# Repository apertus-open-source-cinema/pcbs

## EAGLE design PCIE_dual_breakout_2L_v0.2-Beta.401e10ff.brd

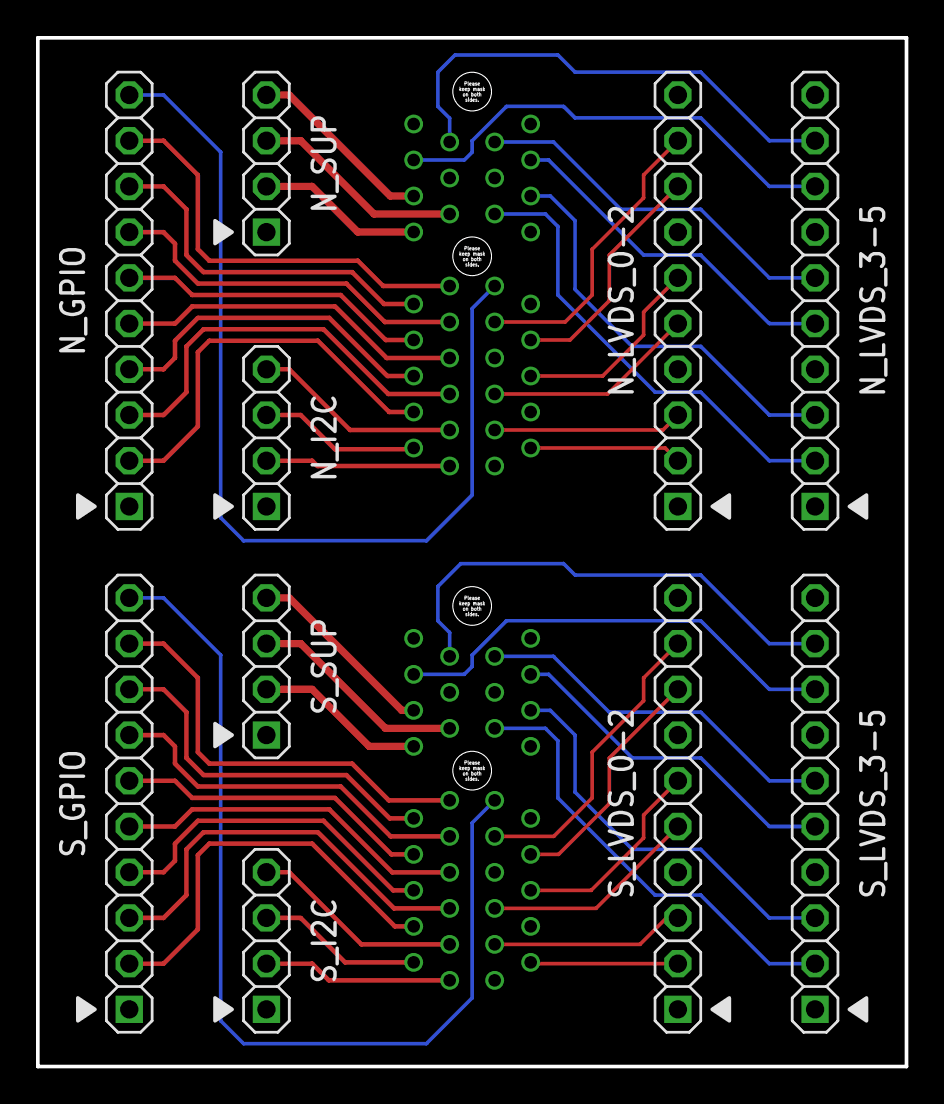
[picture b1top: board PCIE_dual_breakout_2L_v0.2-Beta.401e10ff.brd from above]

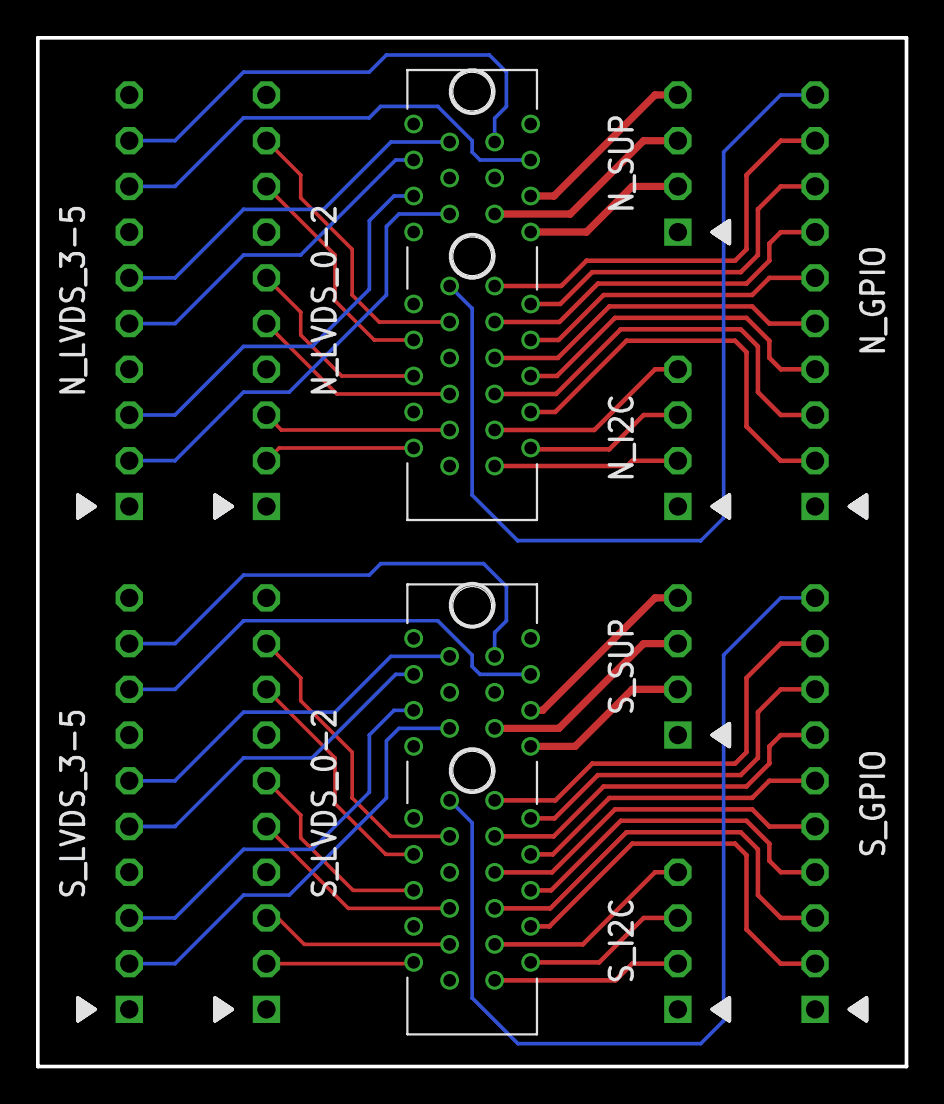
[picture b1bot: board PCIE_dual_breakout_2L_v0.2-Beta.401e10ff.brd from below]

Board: 2 copper layers, 48.3 x 57.1 mm, 12 parts (2 on the bottom side), 54 nets.

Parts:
N_GPIO: 1X10-S
N_I2C: 1X04-S
N_LVDS_0-2, N_LVDS_3-5: 1X10-S
N_SUP: 1X04-S
PCIE-NORTH: PCIE-36-AXIOM-SOCKET; PCIE-36
PCIE-SOUTH: PCIE-36-AXIOM-SOCKET; PCIE-36
S_GPIO: 1X10-S
S_I2C: 1X04-S
S_LVDS_0-2, S_LVDS_3-5: 1X10-S
S_SUP: 1X04-S

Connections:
GND: N_GPIO.1, N_I2C.1, N_LVDS_0-2.1, N_LVDS_0-2.4, N_LVDS_0-2.7, N_LVDS_0-2.10, N_LVDS_3-5.1, N_LVDS_3-5.4, N_LVDS_3-5.7, N_LVDS_3-5.10, N_SUP.1, PCIE-NORTH.A1, PCIE-NORTH.A4, PCIE-NORTH.A7, PCIE-NORTH.A10, PCIE-NORTH.A12, PCIE-NORTH.A15, PCIE-NORTH.A18, PCIE-NORTH.B15, PCIE-NORTH.B18, PCIE-SOUTH.A1, PCIE-SOUTH.A4, PCIE-SOUTH.A7, PCIE-SOUTH.A10, PCIE-SOUTH.A12, PCIE-SOUTH.A15, PCIE-SOUTH.A18, PCIE-SOUTH.B15, PCIE-SOUTH.B18, S_GPIO.1, S_I2C.1, S_LVDS_0-2.1, S_LVDS_0-2.4, S_LVDS_0-2.7, S_LVDS_0-2.10, S_LVDS_3-5.1, S_LVDS_3-5.4, S_LVDS_3-5.7, S_LVDS_3-5.10, S_SUP.1
N_LVDS_0A: N_LVDS_0-2.2, PCIE-NORTH.A2
N_LVDS_0B: N_LVDS_0-2.3, PCIE-NORTH.A3
N_LVDS_1A: N_LVDS_0-2.5, PCIE-NORTH.A5
N_LVDS_1B: N_LVDS_0-2.6, PCIE-NORTH.A6
N_LVDS_2A: N_LVDS_0-2.8, PCIE-NORTH.A8
N_LVDS_2B: N_LVDS_0-2.9, PCIE-NORTH.A9
N_LVDS_3A: N_LVDS_3-5.2, PCIE-NORTH.A13
N_LVDS_3B: N_LVDS_3-5.3, PCIE-NORTH.A14
N_LVDS_4A: N_LVDS_3-5.5, PCIE-NORTH.A16
N_LVDS_4B: N_LVDS_3-5.6, PCIE-NORTH.A17
N_LVDS_5A: N_LVDS_3-5.8, PCIE-NORTH.B16
N_LVDS_5B: N_LVDS_3-5.9, PCIE-NORTH.B17
N_PWRGD: N_GPIO.10, PCIE-NORTH.A11
PCIE_I2C_V: N_I2C.4, PCIE-NORTH.B3, PCIE-SOUTH.B3, S_I2C.4
PCIE_N_5V: N_SUP.2, PCIE-NORTH.B12
PCIE_N_IO0: N_GPIO.2, PCIE-NORTH.B4
PCIE_N_IO1: N_GPIO.3, PCIE-NORTH.B5
PCIE_N_IO2: N_GPIO.4, PCIE-NORTH.B6
PCIE_N_IO3: N_GPIO.5, PCIE-NORTH.B7
PCIE_N_IO4: N_GPIO.6, PCIE-NORTH.B8
PCIE_N_IO5: N_GPIO.7, PCIE-NORTH.B9
PCIE_N_IO6: N_GPIO.8, PCIE-NORTH.B10
PCIE_N_IO7: N_GPIO.9, PCIE-NORTH.B11
PCIE_N_SCL: N_I2C.3, PCIE-NORTH.B2
PCIE_N_SDA: N_I2C.2, PCIE-NORTH.B1
PCIE_N_V: N_SUP.3, PCIE-NORTH.B13
PCIE_N_VCCIO: N_SUP.4, PCIE-NORTH.B14
PCIE_S_5V: PCIE-SOUTH.B12, S_SUP.2
PCIE_S_IO0: PCIE-SOUTH.B4, S_GPIO.2
PCIE_S_IO1: PCIE-SOUTH.B5, S_GPIO.3
PCIE_S_IO2: PCIE-SOUTH.B6, S_GPIO.4
PCIE_S_IO3: PCIE-SOUTH.B7, S_GPIO.5
PCIE_S_IO4: PCIE-SOUTH.B8, S_GPIO.6
PCIE_S_IO5: PCIE-SOUTH.B9, S_GPIO.7
PCIE_S_IO6: PCIE-SOUTH.B10, S_GPIO.8
PCIE_S_IO7: PCIE-SOUTH.B11, S_GPIO.9
PCIE_S_SCL: PCIE-SOUTH.B2, S_I2C.3
PCIE_S_SDA: PCIE-SOUTH.B1, S_I2C.2
PCIE_S_V: PCIE-SOUTH.B13, S_SUP.3
PCIE_S_VCCIO: PCIE-SOUTH.B14, S_SUP.4
S_LVDS_0A: PCIE-SOUTH.A2, S_LVDS_0-2.2
S_LVDS_0B: PCIE-SOUTH.A3, S_LVDS_0-2.3
S_LVDS_1A: PCIE-SOUTH.A5, S_LVDS_0-2.5
S_LVDS_1B: PCIE-SOUTH.A6, S_LVDS_0-2.6
S_LVDS_2A: PCIE-SOUTH.A8, S_LVDS_0-2.8
S_LVDS_2B: PCIE-SOUTH.A9, S_LVDS_0-2.9
S_LVDS_3A: PCIE-SOUTH.A13, S_LVDS_3-5.2
S_LVDS_3B: PCIE-SOUTH.A14, S_LVDS_3-5.3
S_LVDS_4A: PCIE-SOUTH.A16, S_LVDS_3-5.5
S_LVDS_4B: PCIE-SOUTH.A17, S_LVDS_3-5.6
S_LVDS_5A: PCIE-SOUTH.B16, S_LVDS_3-5.8
S_LVDS_5B: PCIE-SOUTH.B17, S_LVDS_3-5.9
S_PWRGD: PCIE-SOUTH.A11, S_GPIO.10

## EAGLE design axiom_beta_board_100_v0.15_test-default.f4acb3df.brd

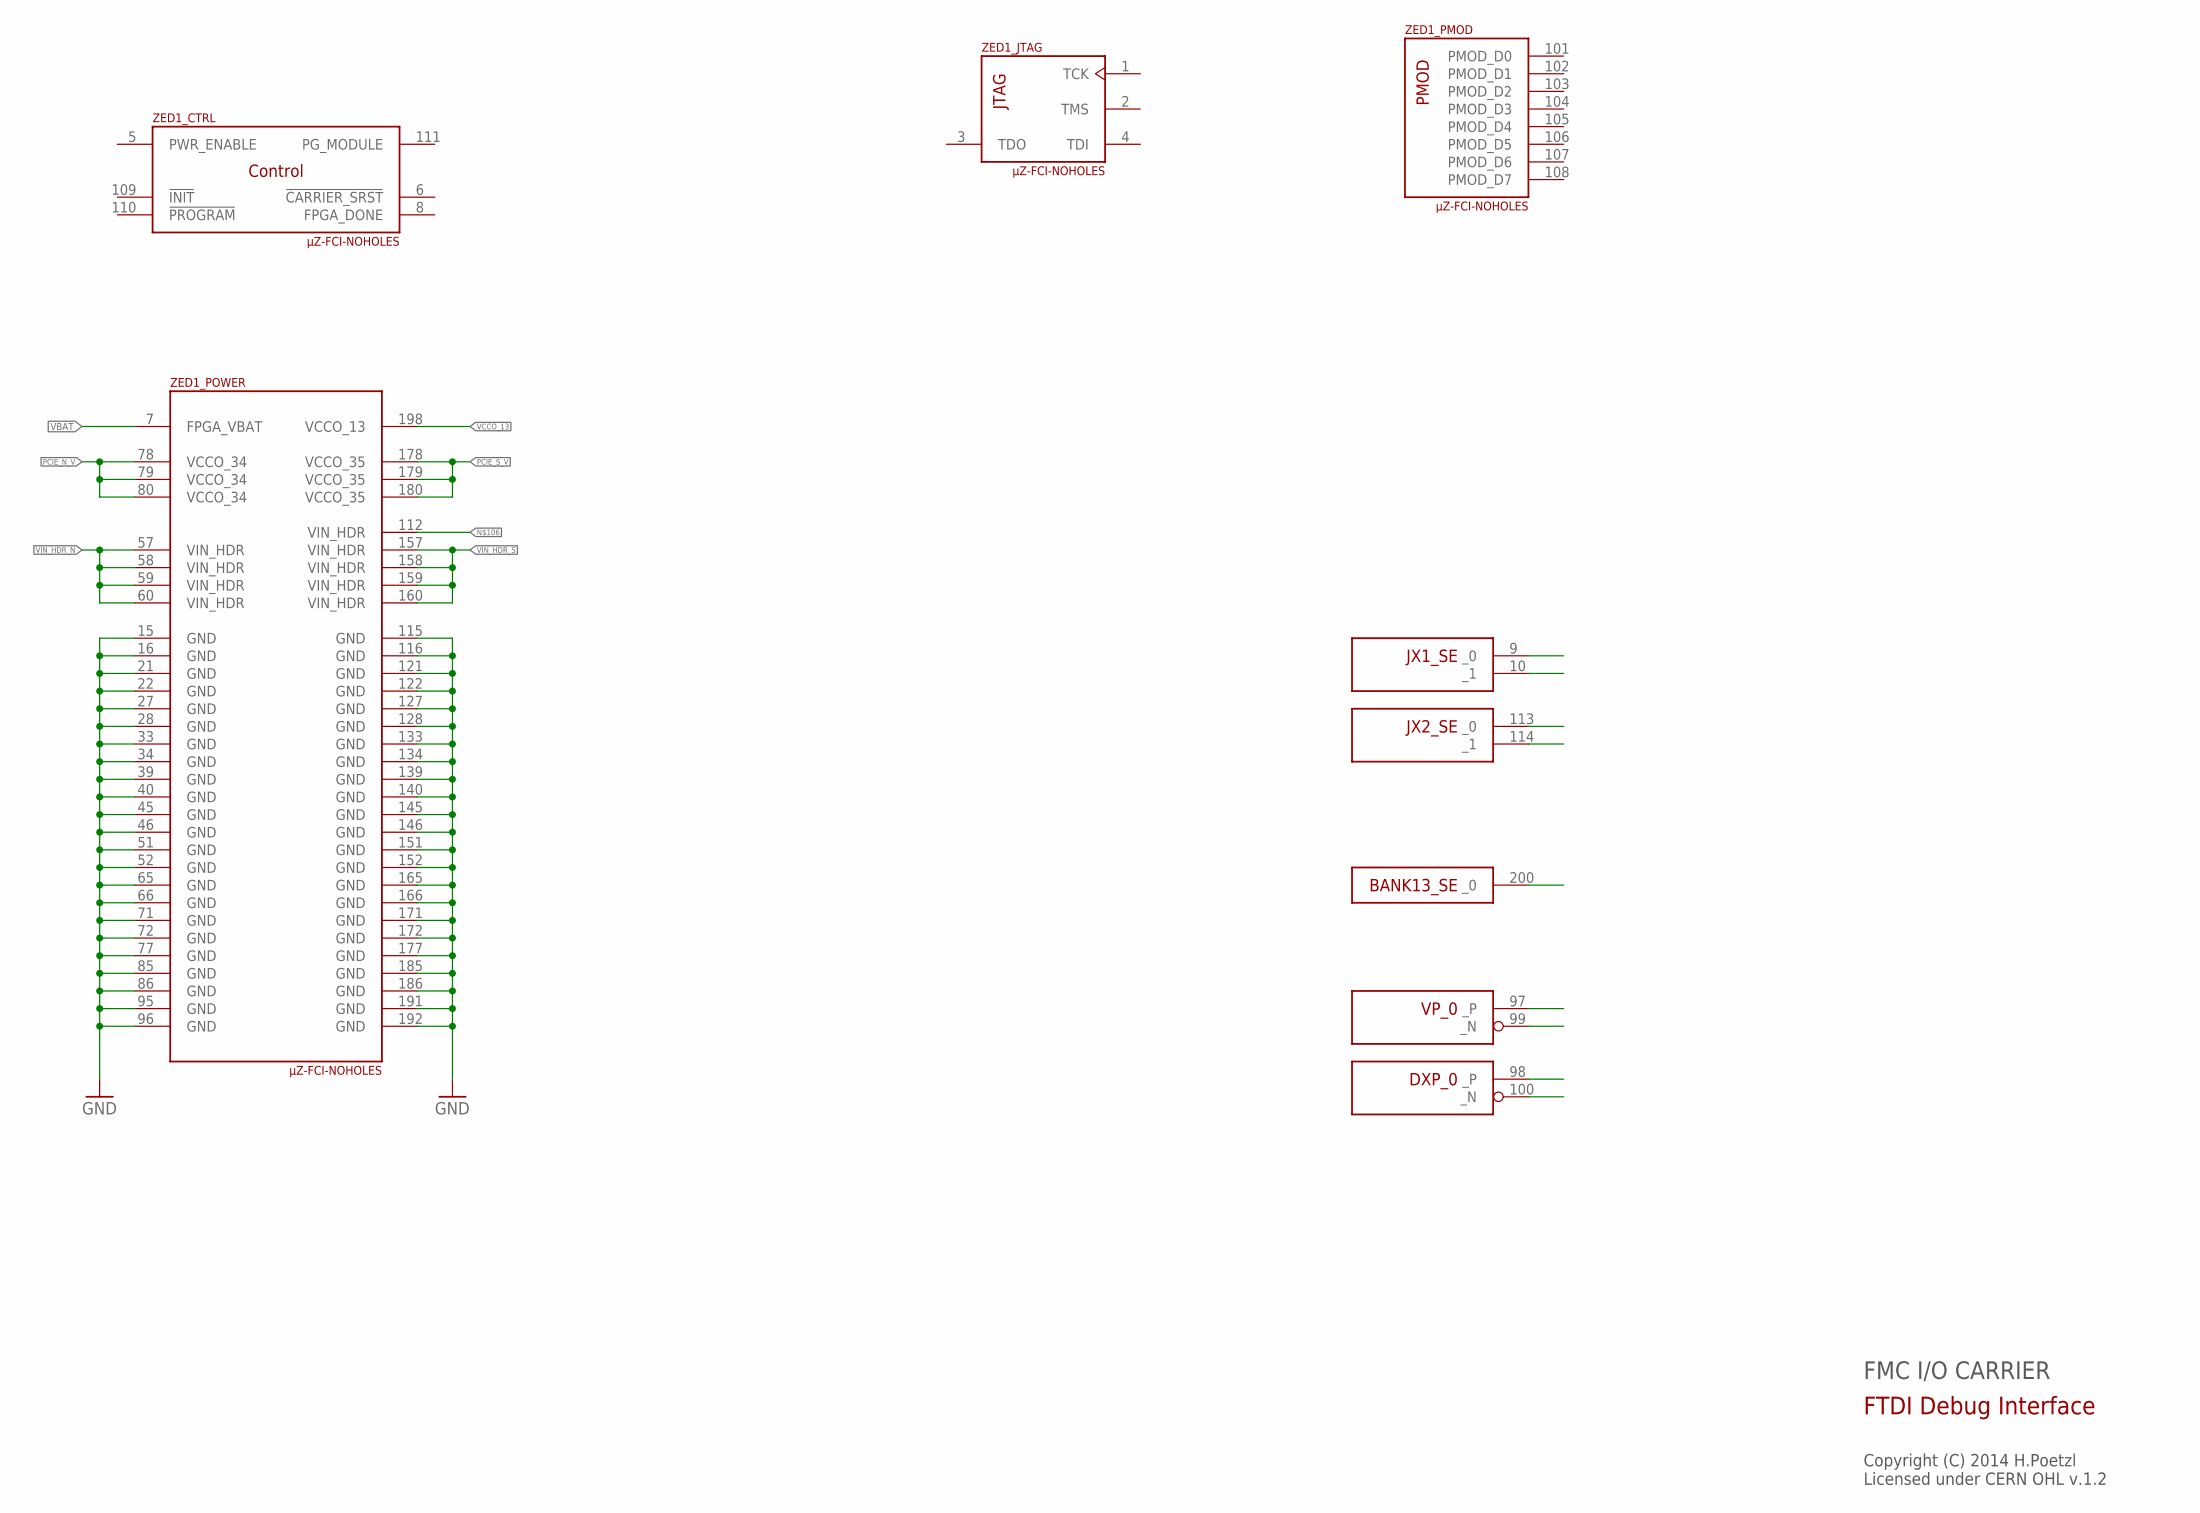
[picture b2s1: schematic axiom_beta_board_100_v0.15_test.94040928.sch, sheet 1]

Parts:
ZED1: µZ-FCI-NOHOLES; µZ-NOHOLES

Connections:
GND: ZED1.15 (GND), ZED1.16 (GND), ZED1.21 (GND), ZED1.22 (GND), ZED1.27 (GND), ZED1.28 (GND), ZED1.33 (GND), ZED1.34 (GND), ZED1.39 (GND), ZED1.40 (GND), ZED1.45 (GND), ZED1.46 (GND), ZED1.51 (GND), ZED1.52 (GND), ZED1.65 (GND), ZED1.66 (GND), ZED1.71 (GND), ZED1.72 (GND), ZED1.77 (GND), ZED1.85 (GND), ZED1.86 (GND), ZED1.95 (GND), ZED1.96 (GND), ZED1.115 (GND), ZED1.116 (GND), ZED1.121 (GND), ZED1.122 (GND), ZED1.127 (GND), ZED1.128 (GND), ZED1.133 (GND), ZED1.134 (GND), ZED1.139 (GND), ZED1.140 (GND), ZED1.145 (GND), ZED1.146 (GND), ZED1.151 (GND), ZED1.152 (GND), ZED1.165 (GND), ZED1.166 (GND), ZED1.171 (GND), ZED1.172 (GND), ZED1.177 (GND), ZED1.185 (GND), ZED1.186 (GND), ZED1.191 (GND), ZED1.192 (GND); also elsewhere on the board
unnamed 266: ZED1.112 (VIN_HDR); also elsewhere on the board
PCIE_N_V: ZED1.78 (VCCO_34), ZED1.79 (VCCO_34), ZED1.80 (VCCO_34); also elsewhere on the board
PCIE_S_V: ZED1.178 (VCCO_35), ZED1.179 (VCCO_35), ZED1.180 (VCCO_35); also elsewhere on the board
VBAT: ZED1.7 (FPGA_VBAT); also elsewhere on the board
VCCO_13: ZED1.198 (VCCO_13)
VIN_HDR_N: ZED1.57 (VIN_HDR), ZED1.58 (VIN_HDR), ZED1.59 (VIN_HDR), ZED1.60 (VIN_HDR); also elsewhere on the board
VIN_HDR_S: ZED1.157 (VIN_HDR), ZED1.158 (VIN_HDR), ZED1.159 (VIN_HDR), ZED1.160 (VIN_HDR); also elsewhere on the board

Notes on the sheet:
FMC I/O CARRIER
Copyright (C) 2014 H.Poetzl Licensed under CERN OHL v.1.2
FTDI Debug Interface

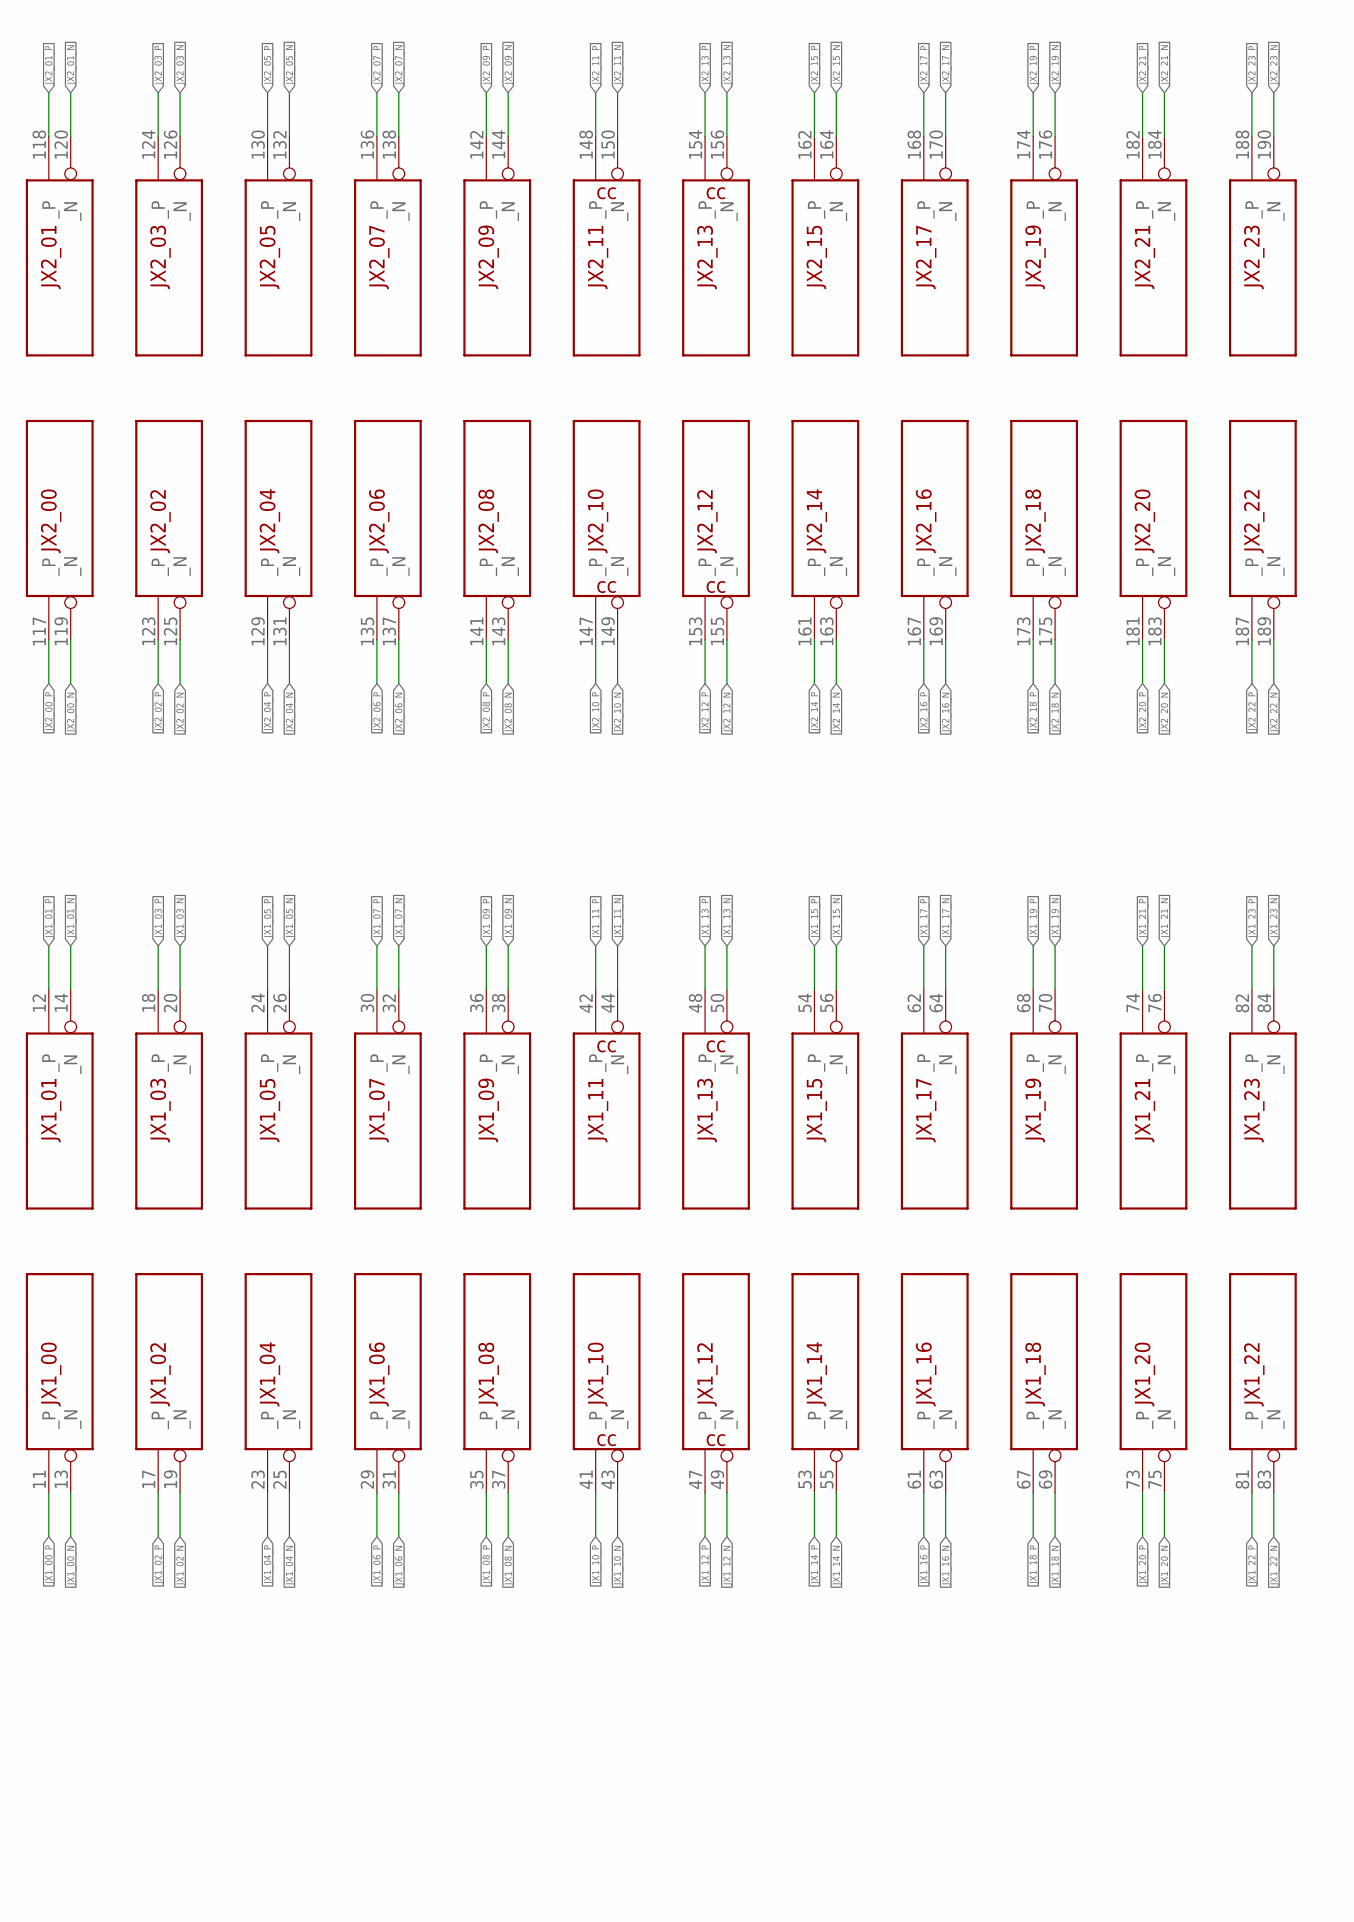
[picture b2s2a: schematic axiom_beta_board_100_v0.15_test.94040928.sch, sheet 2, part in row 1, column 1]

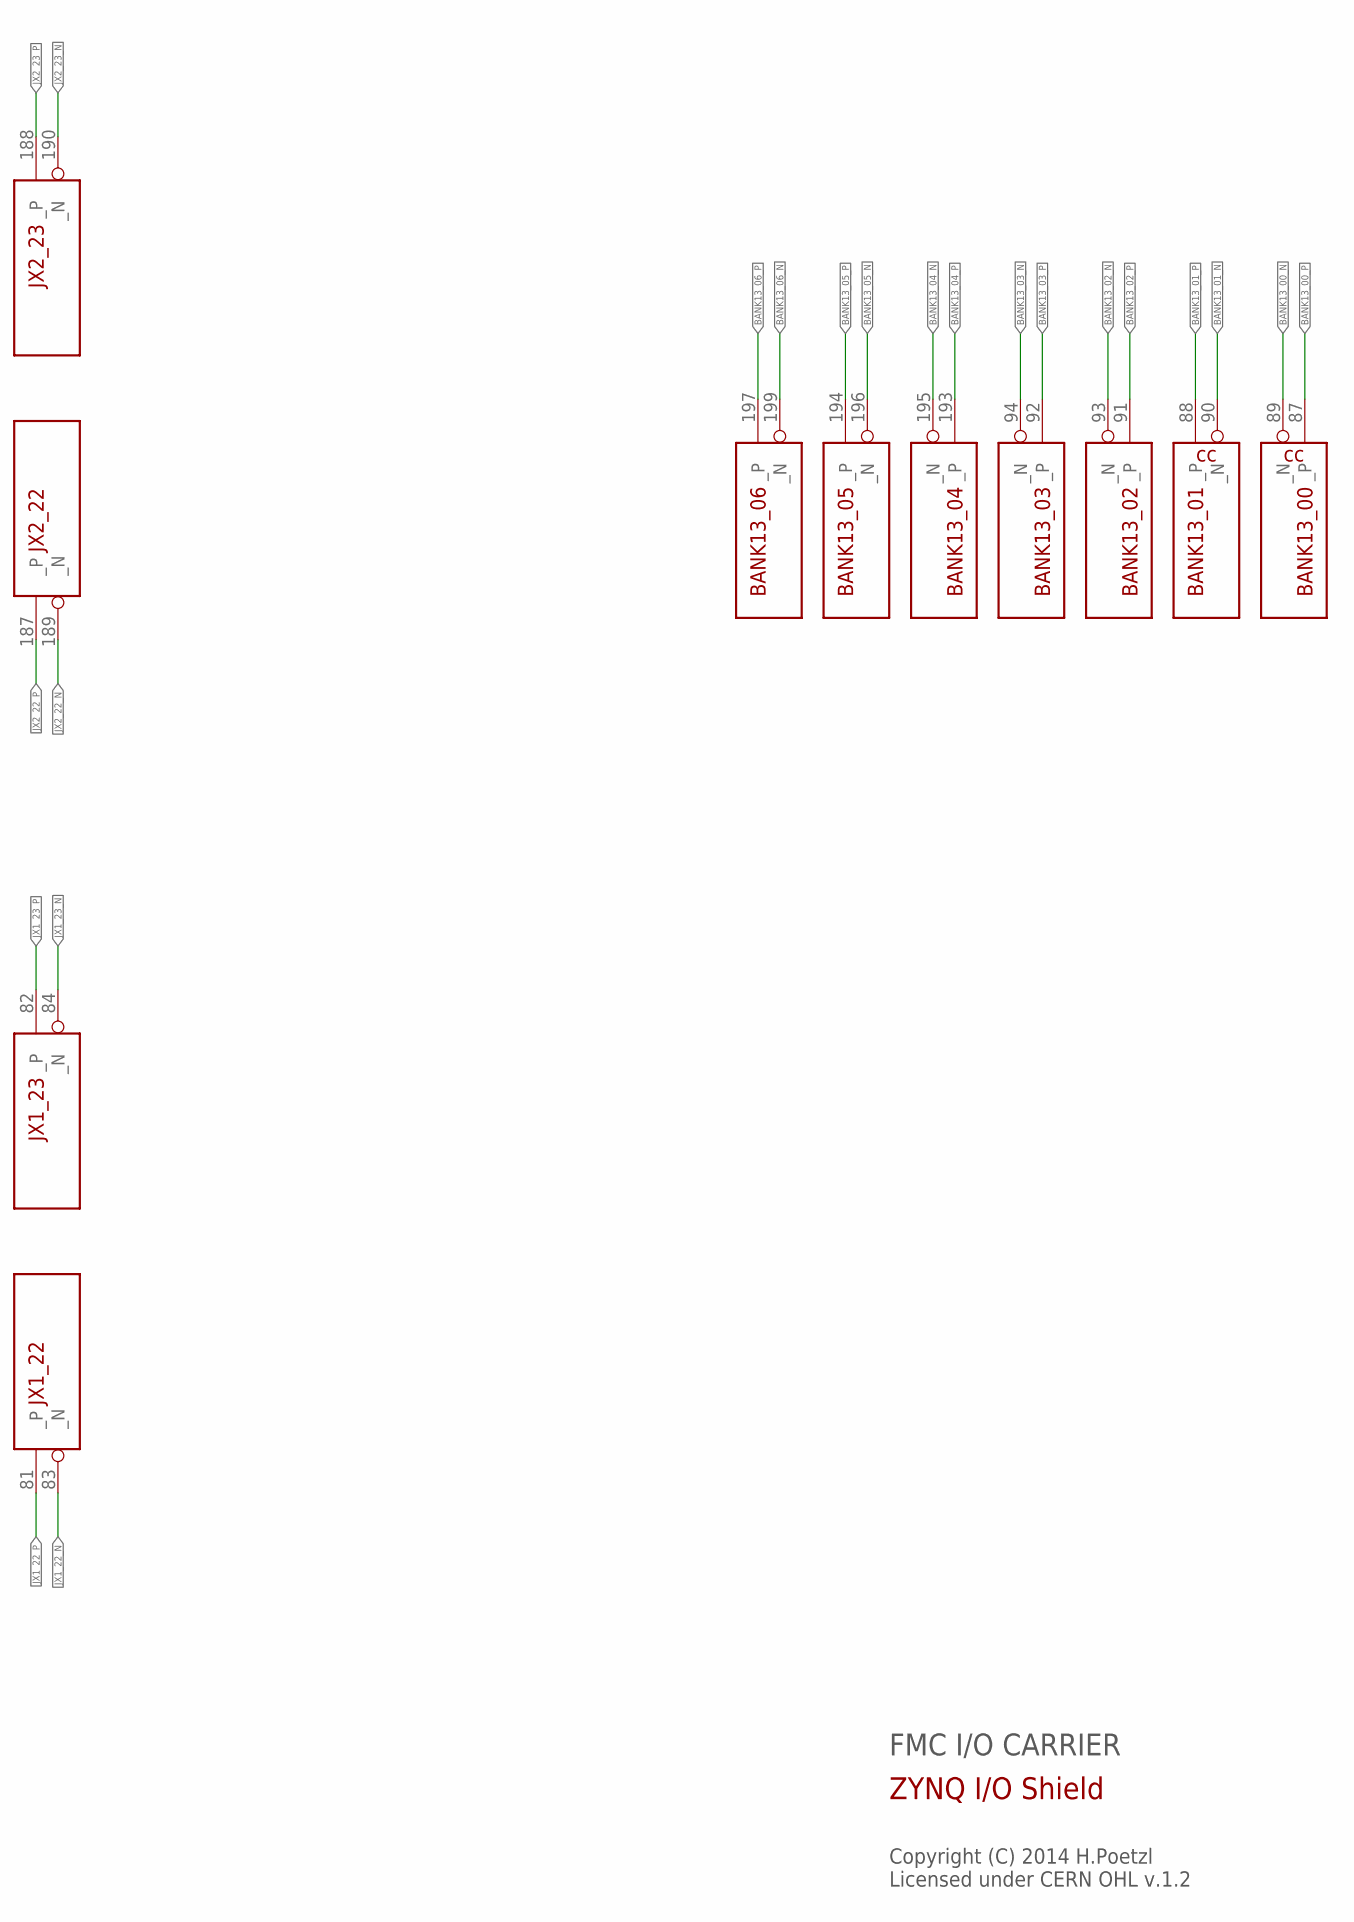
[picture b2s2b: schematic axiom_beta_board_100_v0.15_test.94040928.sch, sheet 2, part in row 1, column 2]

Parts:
ZED1: µZ-FCI-NOHOLES; µZ-NOHOLES

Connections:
BANK13_00_N: ZED1.89 (_N); also elsewhere on the board
BANK13_00_P: ZED1.87 (_P); also elsewhere on the board
BANK13_01_N: ZED1.90 (_N); also elsewhere on the board
BANK13_01_P: ZED1.88 (_P); also elsewhere on the board
BANK13_02_N: ZED1.93 (_N); also elsewhere on the board
BANK13_02_P: ZED1.91 (_P); also elsewhere on the board
BANK13_03_N: ZED1.94 (_N); also elsewhere on the board
BANK13_03_P: ZED1.92 (_P); also elsewhere on the board
BANK13_04_N: ZED1.195 (_N); also elsewhere on the board
BANK13_04_P: ZED1.193 (_P); also elsewhere on the board
BANK13_05_N: ZED1.196 (_N); also elsewhere on the board
BANK13_05_P: ZED1.194 (_P); also elsewhere on the board
BANK13_06_N: ZED1.199 (_N); also elsewhere on the board
BANK13_06_P: ZED1.197 (_P); also elsewhere on the board
JX1_00_N: ZED1.13 (_N); also elsewhere on the board
JX1_00_P: ZED1.11 (_P); also elsewhere on the board
JX1_01_N: ZED1.14 (_N); also elsewhere on the board
JX1_01_P: ZED1.12 (_P); also elsewhere on the board
JX1_02_N: ZED1.19 (_N); also elsewhere on the board
JX1_02_P: ZED1.17 (_P); also elsewhere on the board
JX1_03_N: ZED1.20 (_N); also elsewhere on the board
JX1_03_P: ZED1.18 (_P); also elsewhere on the board
JX1_04_N: ZED1.25 (_N); also elsewhere on the board
JX1_04_P: ZED1.23 (_P); also elsewhere on the board
JX1_05_N: ZED1.26 (_N); also elsewhere on the board
JX1_05_P: ZED1.24 (_P); also elsewhere on the board
JX1_06_N: ZED1.31 (_N); also elsewhere on the board
JX1_06_P: ZED1.29 (_P); also elsewhere on the board
JX1_07_N: ZED1.32 (_N); also elsewhere on the board
JX1_07_P: ZED1.30 (_P); also elsewhere on the board
JX1_08_N: ZED1.37 (_N); also elsewhere on the board
JX1_08_P: ZED1.35 (_P); also elsewhere on the board
JX1_09_N: ZED1.38 (_N); also elsewhere on the board
JX1_09_P: ZED1.36 (_P); also elsewhere on the board
JX1_10_N: ZED1.43 (_N); also elsewhere on the board
JX1_10_P: ZED1.41 (_P); also elsewhere on the board
JX1_11_N: ZED1.44 (_N); also elsewhere on the board
JX1_11_P: ZED1.42 (_P); also elsewhere on the board
JX1_12_N: ZED1.49 (_N); also elsewhere on the board
JX1_12_P: ZED1.47 (_P); also elsewhere on the board
JX1_13_N: ZED1.50 (_N); also elsewhere on the board
JX1_13_P: ZED1.48 (_P); also elsewhere on the board
JX1_14_N: ZED1.55 (_N); also elsewhere on the board
JX1_14_P: ZED1.53 (_P); also elsewhere on the board
JX1_15_N: ZED1.56 (_N); also elsewhere on the board
JX1_15_P: ZED1.54 (_P); also elsewhere on the board
JX1_16_N: ZED1.63 (_N); also elsewhere on the board
JX1_16_P: ZED1.61 (_P); also elsewhere on the board
JX1_17_N: ZED1.64 (_N); also elsewhere on the board
JX1_17_P: ZED1.62 (_P); also elsewhere on the board
JX1_18_N: ZED1.69 (_N); also elsewhere on the board
JX1_18_P: ZED1.67 (_P); also elsewhere on the board
JX1_19_N: ZED1.70 (_N); also elsewhere on the board
JX1_19_P: ZED1.68 (_P); also elsewhere on the board
JX1_20_N: ZED1.75 (_N); also elsewhere on the board
JX1_20_P: ZED1.73 (_P); also elsewhere on the board
JX1_21_N: ZED1.76 (_N); also elsewhere on the board
JX1_21_P: ZED1.74 (_P); also elsewhere on the board
JX1_22_N: ZED1.83 (_N); also elsewhere on the board
JX1_22_P: ZED1.81 (_P); also elsewhere on the board
JX1_23_N: ZED1.84 (_N); also elsewhere on the board
JX1_23_P: ZED1.82 (_P); also elsewhere on the board
JX2_00_N: ZED1.119 (_N); also elsewhere on the board
JX2_00_P: ZED1.117 (_P); also elsewhere on the board
JX2_01_N: ZED1.120 (_N); also elsewhere on the board
JX2_01_P: ZED1.118 (_P); also elsewhere on the board
JX2_02_N: ZED1.125 (_N); also elsewhere on the board
JX2_02_P: ZED1.123 (_P); also elsewhere on the board
JX2_03_N: ZED1.126 (_N); also elsewhere on the board
JX2_03_P: ZED1.124 (_P); also elsewhere on the board
JX2_04_N: ZED1.131 (_N); also elsewhere on the board
JX2_04_P: ZED1.129 (_P); also elsewhere on the board
JX2_05_N: ZED1.132 (_N); also elsewhere on the board
JX2_05_P: ZED1.130 (_P); also elsewhere on the board
JX2_06_N: ZED1.137 (_N); also elsewhere on the board
JX2_06_P: ZED1.135 (_P); also elsewhere on the board
JX2_07_N: ZED1.138 (_N); also elsewhere on the board
JX2_07_P: ZED1.136 (_P); also elsewhere on the board
JX2_08_N: ZED1.143 (_N); also elsewhere on the board
JX2_08_P: ZED1.141 (_P); also elsewhere on the board
JX2_09_N: ZED1.144 (_N); also elsewhere on the board
JX2_09_P: ZED1.142 (_P); also elsewhere on the board
JX2_10_N: ZED1.149 (_N); also elsewhere on the board
JX2_10_P: ZED1.147 (_P); also elsewhere on the board
JX2_11_N: ZED1.150 (_N); also elsewhere on the board
JX2_11_P: ZED1.148 (_P); also elsewhere on the board
JX2_12_N: ZED1.155 (_N); also elsewhere on the board
JX2_12_P: ZED1.153 (_P); also elsewhere on the board
JX2_13_N: ZED1.156 (_N); also elsewhere on the board
JX2_13_P: ZED1.154 (_P); also elsewhere on the board
JX2_14_N: ZED1.163 (_N); also elsewhere on the board
JX2_14_P: ZED1.161 (_P); also elsewhere on the board
JX2_15_N: ZED1.164 (_N); also elsewhere on the board
JX2_15_P: ZED1.162 (_P); also elsewhere on the board
JX2_16_N: ZED1.169 (_N); also elsewhere on the board
JX2_16_P: ZED1.167 (_P); also elsewhere on the board
JX2_17_N: ZED1.170 (_N); also elsewhere on the board
JX2_17_P: ZED1.168 (_P); also elsewhere on the board
JX2_18_N: ZED1.175 (_N); also elsewhere on the board
JX2_18_P: ZED1.173 (_P); also elsewhere on the board
JX2_19_N: ZED1.176 (_N); also elsewhere on the board
JX2_19_P: ZED1.174 (_P); also elsewhere on the board
JX2_20_N: ZED1.183 (_N); also elsewhere on the board
JX2_20_P: ZED1.181 (_P); also elsewhere on the board
JX2_21_N: ZED1.184 (_N); also elsewhere on the board
JX2_21_P: ZED1.182 (_P); also elsewhere on the board
JX2_22_N: ZED1.189 (_N); also elsewhere on the board
JX2_22_P: ZED1.187 (_P); also elsewhere on the board
JX2_23_N: ZED1.190 (_N); also elsewhere on the board
JX2_23_P: ZED1.188 (_P); also elsewhere on the board

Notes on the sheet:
FMC I/O CARRIER
Copyright (C) 2014 H.Poetzl Licensed under CERN OHL v.1.2
ZYNQ I/O Shield

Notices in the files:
axiom_beta_board_100_v0.15_test-default.f4acb3df.brd:
Copyright (C) 2015 Herbert Pötzl
axiom_beta_board_100_v0.16_test.005b8144.sch:
Copyright (C) 2015 H.Poetzl
axiom_beta_board_100_v0.7_test-default.3b98ab8b.brd:
Copyright (C) 2014 Herbert Pötzl
parts and their libraries:
microbuilder: This work is placed in the public domain, and may be freely used for commercial and non-commercial work with the following conditions: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
